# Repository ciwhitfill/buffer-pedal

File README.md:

# JFET Buffer

This project documents the design and construction of a JFET buffer guitar pedal.

## BOM
|Quantity |Designators |Description         |Value         |Package |Mouser Part #       |
|:--------|:-----------|:-------------------|:-------------|:-------|:-------------------|
|3        |R1, R2, R3  |Resistor            |10Mohm, 1/8W  |3.6mm   |594-5063JD10M00FT   |
|1        |R 5         |Resistor            |330ohms, 1/8W |3.6mm   |603-MFR-12FTF52-330R|
|1        |R6          |Resistor            |100Kohms, 1/8W|3.6mm   |603-CFR-12JT-52-100K|
|1        |R7          |Resistor            |4.7Kohms, 1/8W|3.6mm   |603-MFR-12FTF52-4K7 |
|2        |C1, C2      |Capacitor, polarized|10uF, 16V     |4mm     |647-USW1C100MDD     |
|1        |C3          |Capacitor, polarized|47uF, 25V     |5mm     |647-UFW1E470MDD     |
|2        |Q1, Q2      |N-Channel JFET      |J113          |TO-92   |512-J113            |
|1        |D1          |Diode               |1N4003        |DO-41   |583-1N4003-T        |
|1        |D2          |LED                 |Green         |5mm     |859-LTL2R3KGD-EM    |
|2        |J1, J2      |Phone Connector     |1/4" TS       |        |568-NYS229          |
|1        |J3          |DC Power Connector  |2.1mm         |        |163-1060-EX         |

## Design

The circuit consists of a JFET source follower with an active load. Compared to passive biasing, an active load provides an operating point that is stable over a much larger range of voltages. This allows the amplifier to drive lower impedance loads at lower supply voltages.

## Simulation Results
The following simulations were conducted in LTspice. For the schematic file and simulation results, [see the simulation folder.](./simulation)

### Input Impedance 
A high input impedance is necessary to avoid loading passive guitar pickups. Generally, an input impedance of at least 1 MΩ is desired. The design provides this impedance throughout the audio range.

### Output Impedance
The design provides a low enough output impedance to drive line-level inputs. While the coupling capacitor dominates at low frequencies, the output impedance asymptotes to 100 Ω, which is more than sufficient for instrument level applications.

### Gain
A good voltage buffer has as close to a gain of 1 as possible. Due to the higher impedance of the active load, the design comes within 0.1 dB of this.

### Power Supply Rejection
The design has a PSRR of -43dB at DC, and the power supply capacitor further filters supply noise at high frequencies.

### Noise
Noise simulation results in 171.18 nV in the audio range. Even if actual circuit noise is many times worse, it will be negligible compared to other noise sources in the signal chain.

## Testing

When a 1 V, 1 kHz test signal is applied to the input, the buffer reproduces it at the output within the precision of the test equipment available.

When overdriven, the buffer clips asymmetically, resulting in predominantly 2nd-order harmonic distortion. In guitar circuits, this is generally preferred to the odd-order distortion of amplifiers with high loop gain.

### Frequency Response
In practice, the amplifier exhibits mild roll-off of sub-bass frequencies below 30 Hz. This is well below the necessary bandwidth of a guitar amplifier. The high-end frequency response extends well above the audio band, ensuring accurate phase response.

## Assembly

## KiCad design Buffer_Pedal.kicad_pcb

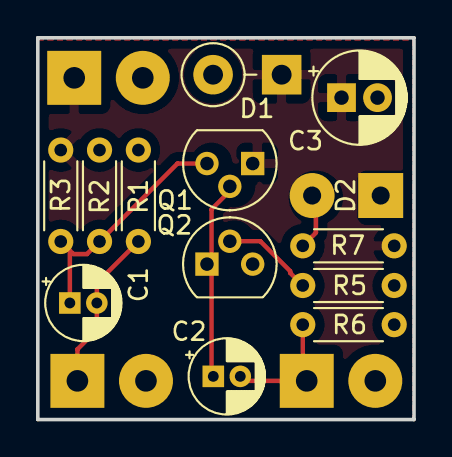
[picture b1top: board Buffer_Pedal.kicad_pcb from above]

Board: 2 copper layers, 20.9 x 21.2 mm, 16 parts (0 on the bottom side), 8 nets.

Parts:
C1, C2: 10u; CP_Radial_D4.0mm_P1.50mm
C3: 47u; CP_Radial_D5.0mm_P2.00mm
D1: 1N4003; D_DO-41_SOD81_P3.81mm_Vertical_KathodeUp
D2: LED; SolderWirePad_1x02_P3.81mm_Drill1mm
IN: In; SolderWirePad_1x02_P3.81mm_Drill1.2mm
OUT: Out; SolderWirePad_1x02_P3.81mm_Drill1.2mm
PWR: 9V; SolderWirePad_1x02_P3.81mm_Drill1.2mm
Q1, Q2: J113; TO-92
R1, R2, R3: 10M; R_Axial_DIN0204_L3.6mm_D1.6mm_P5.08mm_Horizontal
R5: 330; R_Axial_DIN0204_L3.6mm_D1.6mm_P5.08mm_Horizontal
R6: 100k; R_Axial_DIN0204_L3.6mm_D1.6mm_P5.08mm_Horizontal
R7: 4.7k; R_Axial_DIN0204_L3.6mm_D1.6mm_P5.08mm_Horizontal

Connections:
GND: C3.2, D1.2, D2.1, IN.2, OUT.2, PWR.2, Q2.3, R1.1, R2.2, R5.2, R6.2
unnamed: C1.1, Q1.3, R2.1, R3.2
unnamed: C1.2, IN.1, R1.2
unnamed: C2.1, Q1.2, Q2.1
unnamed: C2.2, OUT.1, R6.1
unnamed: D2.2, R7.1
unnamed: Q2.2, R5.1
PWR: C3.1, D1.1, PWR.1, Q1.1, R3.1, R7.2

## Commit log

2019-12-29 Initial Commit 2
2019-12-29 Fixed bug in graph code
2019-12-29 simulation graphs
2019-12-29 added .gitattributes
2019-12-29 added schematic image
2019-12-30 Preliminary documention
2019-12-30 Preliminary documentation
2019-12-30 added BOM, PCB render
2019-12-30 corrected power jack polarity
2019-12-30 moved BOM to top of readme
2019-12-31 changed DC power jack in BOM
    metal jack body + center negative = ground short
2020-01-01 fixed JFET pinout
2020-01-02 updated schematic and layout
2020-01-02 fixed cursor in schematic image
2020-02-01 lab measurements
2020-02-02 remove .vscode
2020-02-02 graphed lab measurements
2020-02-02 added interpolation
2020-02-02 added lab measurements
2020-02-02 updated gain image
2020-02-02 added pcb image
2020-03-28 larger D2 footprint
